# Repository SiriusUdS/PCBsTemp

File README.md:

# STM32 Rocket Engine Control Template

Template repository for STM32 embedded development projects focused on rocket engine control systems. This project uses CMake and is structured with a layered architecture for maintainability and modularity.

Repository name format: `<stm[model]|py|desktop>-<project_name>-<layer>`

## Project Structure

The project follows a layered architecture with clear separation of concerns:

```
├── src/
│   ├── HAL/              # Hardware Abstraction Layer
│   ├── Components/       # Hardware component drivers
│   ├── DIL/              # Device Interface Layer
│   └── Controller/       # Application logic and control algorithms
├── include/
│   ├── HAL/
│   ├── Components/
│   ├── DIL/
│   └── Controller/
├── cmake/                # CMake toolchain files
├── CMakeLists.txt        # Main build configuration
├── startup_stm32f407xx.s # Startup assembly file
└── STM32F407VGTx_FLASH.ld # Linker script
```

### Architecture Layers

#### 1. HAL (Hardware Abstraction Layer)
- Lowest level interface to hardware peripherals
- Direct access to STM32 registers and peripherals
- Provides basic initialization and control functions for GPIO, timers, ADC, UART, etc.

**Files:**
- `include/HAL/hal_init.h`
- `src/HAL/hal_init.c`
- `include/HAL/stm32f4xx.h`

#### 2. Components Layer
- Hardware component drivers for sensors, actuators, and communication modules
- Abstracts specific hardware components (sensors, valves, etc.)
- Uses HAL layer for low-level operations

**Files:**
- `include/Components/sensors.h`
- `src/Components/sensors.c`

#### 3. DIL (Device Interface Layer)
- High-level, abstract interface to devices
- Hides component-specific implementation details
- Provides logical device operations (e.g., engine control, valve management)

**Files:**
- `include/DIL/engine_interface.h`
- `src/DIL/engine_interface.c`

#### 4. Controller Layer
- Highest level application logic
- Implements control algorithms and state machines
- Orchestrates all lower layers for complete application functionality

**Files:**
- `include/Controller/controller.h`
- `src/Controller/controller.c`

## Prerequisites

### Required Software

1. **ARM GCC Toolchain**
   - Download from: https://developer.arm.com/tools-and-software/open-source-software/developer-tools/gnu-toolchain/gnu-rm
   - Add to system PATH

2. **CMake** (version 3.20 or higher)
   - Download from: https://cmake.org/download/
   - Or install via package manager:
     ```bash
     # Ubuntu/Debian
     sudo apt-get install cmake
     
     # macOS
     brew install cmake
     ```

3. **Build Tools**
   - Linux: `sudo apt-get install build-essential`
   - macOS: Install Xcode Command Line Tools
   - Windows: Install MinGW or use WSL

4. **ST-Link Utility** (for flashing)
   - Download from STMicroelectronics website
   - Or use OpenOCD: `sudo apt-get install openocd`

### Optional Tools

- **STM32CubeMX**: For peripheral configuration and HAL code generation
- **Serial Terminal**: PuTTY, minicom, or screen for UART communication
- **IDE**: Visual Studio Code, CLion, or STM32CubeIDE

## Setup Instructions

### 1. Clone the Repository

```bash
git clone <repository-url>
cd template
```

### 2. Configure for Your Target MCU

Edit `CMakeLists.txt` to match your specific STM32 target:

```cmake
# Update these lines for your MCU
set(MCU_FAMILY STM32F4xx)
set(MCU_MODEL STM32F407xx)
set(MCU_LINKER_SCRIPT "${CMAKE_SOURCE_DIR}/STM32F407VGTx_FLASH.ld")
```

If using a different STM32 model:
1. Update the linker script (`.ld` file) with correct memory sizes
2. Update the startup file (`.s` file) with correct vector table
3. Update CPU flags in CMakeLists.txt if needed

### 3. Build the Project

#### Using Command Line

```bash
# Create build directory
mkdir build
cd build

# Configure CMake with ARM toolchain
cmake .. -DCMAKE_TOOLCHAIN_FILE=../cmake/arm-none-eabi-gcc.cmake

# Build the project
cmake --build .
```

This will generate:
- `STM32_RocketEngine.elf` - ELF executable
- `STM32_RocketEngine.hex` - Intel HEX format for flashing
- `STM32_RocketEngine.bin` - Binary format for flashing
- `STM32_RocketEngine.map` - Memory map file

#### Using Make

```bash
cd build
make
```

### 4. Flash to MCU

#### Using ST-Link

```bash
# Using st-flash
st-flash write STM32_RocketEngine.bin 0x8000000

# Or using OpenOCD
openocd -f interface/stlink.cfg -f target/stm32f4x.cfg -c "program STM32_RocketEngine.elf verify reset exit"
```

#### Using STM32CubeProgrammer

1. Open STM32CubeProgrammer
2. Connect to the board via ST-Link
3. Load the `.hex` or `.bin` file
4. Click "Download"

### 5. Debug

#### Using GDB

```bash
# Start OpenOCD (in one terminal)
openocd -f interface/stlink.cfg -f target/stm32f4x.cfg

# Start GDB (in another terminal)
arm-none-eabi-gdb build/STM32_RocketEngine.elf
(gdb) target remote localhost:3333
(gdb) monitor reset halt
(gdb) load
(gdb) continue
```

## Development Workflow

### Adding New Features

1. **New Sensor/Component**
   - Add header in `include/Components/`
   - Implement in `src/Components/`
   - Update CMakeLists.txt if needed

2. **New Device Interface**
   - Add header in `include/DIL/`
   - Implement in `src/DIL/`
   - Use Components layer functions

3. **New Control Logic**
   - Add to `include/Controller/controller.h`
   - Implement in `src/Controller/controller.c`
   - Use DIL functions

### Customization

#### Changing MCU Target

1. Update `CMakeLists.txt`:
   - Change `MCU_FAMILY` and `MCU_MODEL`
   - Update CPU flags (`CPU`, `FPU`, `FLOAT_ABI`)
   
2. Replace linker script (`.ld`) with your MCU's memory layout

3. Replace startup file (`.s`) with your MCU's vector table

4. Update `stm32f4xx.h` or include proper CMSIS headers

#### Adding STM32 HAL Library

If you want to use the official STM32 HAL library:

1. Download STM32CubeF4 package
2. Copy HAL sources to your project
3. Update CMakeLists.txt to include HAL sources
4. Replace minimal `stm32f4xx.h` with official CMSIS headers

## Project Configuration

### Compiler Flags

Defined in `CMakeLists.txt`:
- `-Wall -Wextra`: Enable warnings
- `-fdata-sections -ffunction-sections`: Enable garbage collection of unused sections
- `-O0 -g3`: Debug build (no optimization, full debug info)
- `-O2`: Release build (optimize for speed)

### Linker Flags

- `-specs=nano.specs`: Use newlib-nano for smaller code size
- `--gc-sections`: Remove unused sections
- `-Wl,-Map=`: Generate map file

## Troubleshooting

### Build Errors

**"arm-none-eabi-gcc not found"**
- Install ARM GCC toolchain and add to PATH
- Verify with: `arm-none-eabi-gcc --version`

**"undefined reference to"**
- Check that all source files are included in CMakeLists.txt
- Verify function declarations match implementations

### Flash Errors

**"Could not find device"**
- Check ST-Link connection
- Install ST-Link drivers
- Try different USB port

**"Flash loader run error"**
- Verify correct linker script for your MCU
- Check memory addresses in linker script
- Ensure binary size doesn't exceed flash memory

### Runtime Issues

**Program doesn't start**
- Check vector table location
- Verify startup code matches MCU
- Check clock configuration

**Hard fault**
- Enable fault handlers in startup code
- Use debugger to find fault location
- Check stack size in linker script

## Additional Resources

- [STM32F4 Reference Manual](https://www.st.com/resource/en/reference_manual/dm00031020.pdf)
- [ARM Cortex-M4 Technical Reference Manual](https://developer.arm.com/documentation/100166/0001/)
- [CMake Documentation](https://cmake.org/documentation/)
- [GNU ARM Embedded Toolchain](https://developer.arm.com/tools-and-software/open-source-software/developer-tools/gnu-toolchain/gnu-rm)

## Safety Notice

This template is designed for rocket engine control systems. Always follow proper safety protocols:
- Implement multiple safety interlocks
- Test thoroughly in simulation before hardware testing
- Have emergency shutdown procedures
- Follow all applicable regulations and safety standards
- Never operate engine systems without proper safety equipment and trained personnel

## License

This is a template project. Add your license information here.

## Contributing

Contributions are welcome. Please follow the existing code structure and layered architecture when submitting changes.

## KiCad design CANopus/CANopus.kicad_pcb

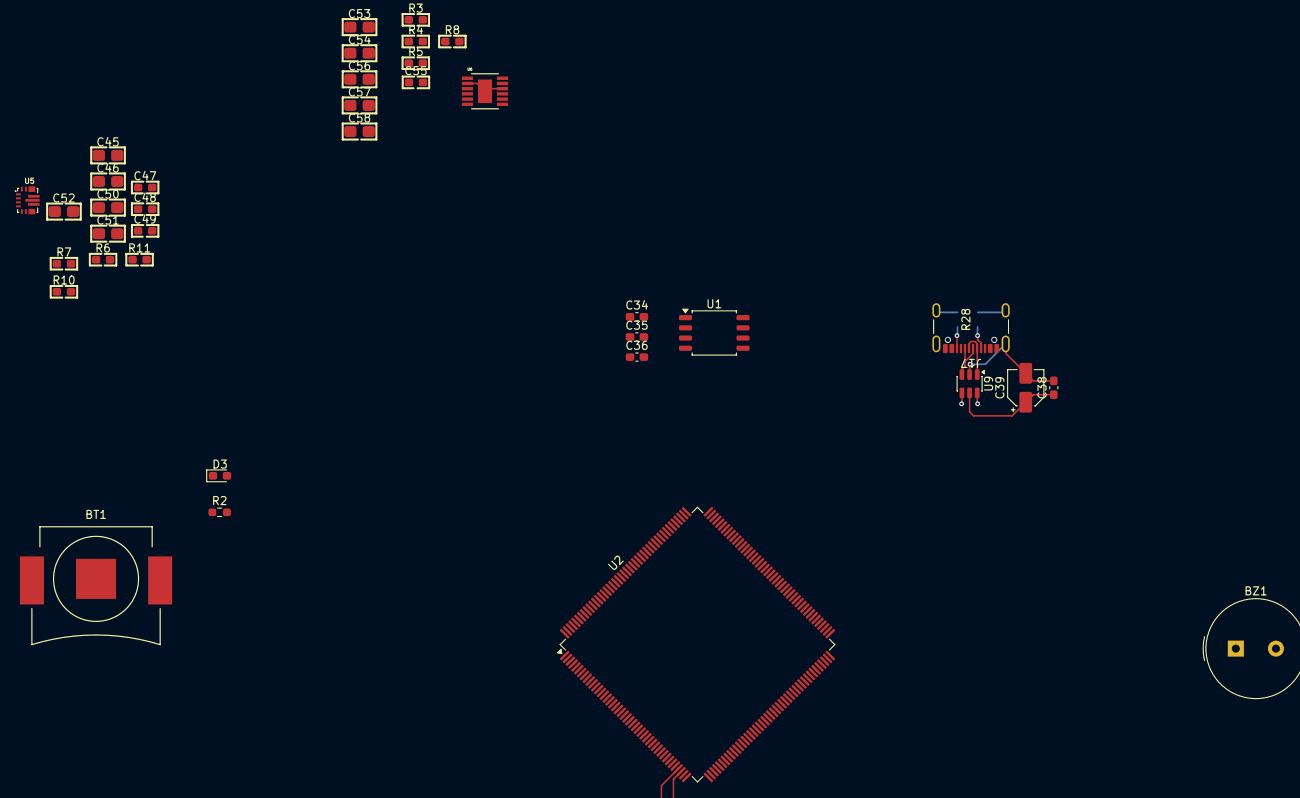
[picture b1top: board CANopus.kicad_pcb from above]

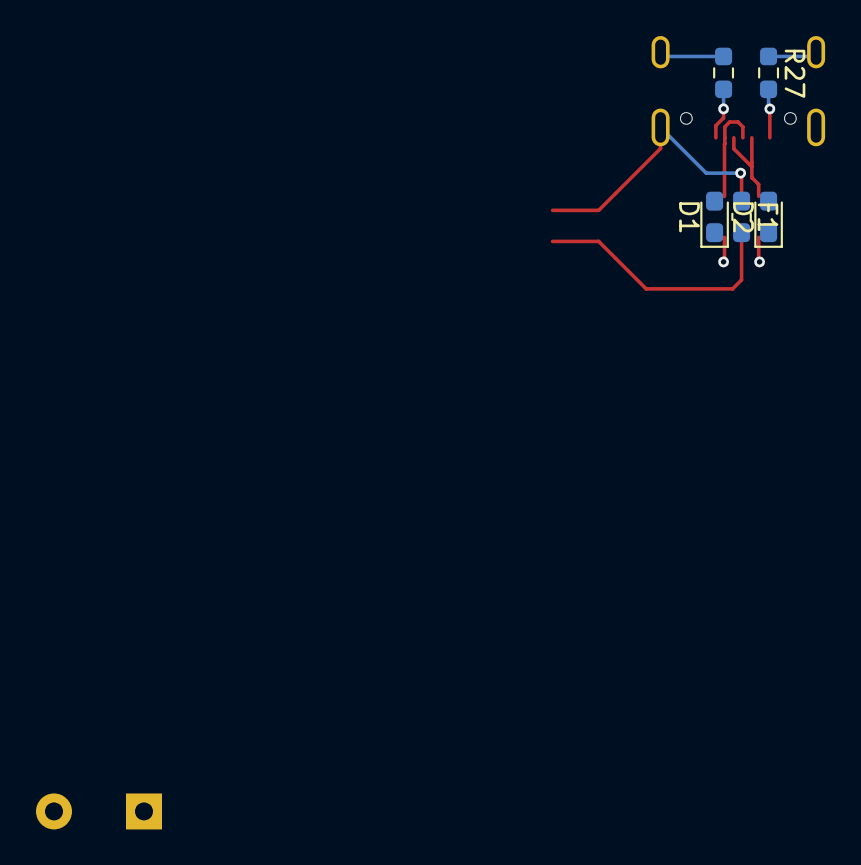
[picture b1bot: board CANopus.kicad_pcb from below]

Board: 2 copper layers, 42 parts (5 on the bottom side), 26 nets.

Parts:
BT1: Battery_Holder_1025; BatteryHolder_BHX1_1025
BZ1: Buzzer_TDK_PS1240; Buzzer_TDK_PS1240P02BT_D12.2mmP5mm
C34: 0.1u; C_0603_1608Metric_Pad1.08x0.95mm_HandSolder
C35, C38: 0.1uF; C_0603_1608Metric_Pad1.08x0.95mm_HandSolder
C36: 0.47uF; C_0603_1608Metric_Pad1.08x0.95mm_HandSolder
C39: 10uF/50V; CP_Elec_4x5.4
C45, C46: 10u; C0805_MAN
C47, C49: 10u; C0603_MAN
C48, C55: 100n; C0603_MAN
C50, C51, C52: 22u; C0805_MAN
C53, C54: 4.7u; C0805_MAN
C56: 390pF; C0805_MAN
C57: 10pF; C0805_MAN
C58: 22uF; C0805_MAN
D1: D; D_0603_1608Metric_Pad1.05x0.95mm_HandSolder
D2, D3: 6.4V; D_0603_1608Metric_Pad1.05x0.95mm_HandSolder
F1: Polyfuse; Fuse_0603_1608Metric_Pad1.05x0.95mm_HandSolder
J17: USB_C_Receptacle_USB2.0_man; USB_C_Receptacle_GCT_USB4105-xx-A_16P_TopMnt_Horizontal
R2: 10k; R_0603_1608Metric_Pad0.98x0.95mm_HandSolder
R3: 57.6k; R0603_MAN
R4, R5: x; R0603_MAN
R6: 470k; R0603_MAN
R7: 10k; R0603_MAN
R8: 210k; R0603_MAN
R10: 100k; R0603_MAN
R11: 150k; R0603_MAN
R27, R28: 5.1k; R_0603_1608Metric_Pad0.98x0.95mm_HandSolder
U1: SST25VF080B-50-4x-S2Ax; SOIC-8_5.3x5.3mm_P1.27mm
U2: STM32H747IITx; LQFP-176_24x24mm_P0.5mm
U5: TPS63070RNMT; QFN50P250X300X100-15N
U6: MSOP-12_MSE
U9: USBLC6-2SC6; SOT-23-6

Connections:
+3.3V: C49.1, C50.1, C51.1, C52.1, R6.1, R10.1
+3V3: C34.1, C35.1, C36.1, U1.8 (VDD)
+5V: C38.1, C39.1, D1.1 (K), U9.5 (VBUS)
+BATT: C45.1, C46.1, C47.1, R7.1
/ECU_Power/3.3V_FB: R6.2, R11.1
/USB_D+: J17.A6 (D+), J17.B6 (D+), U9.3 (I/O2)
/USB_D-: J17.A7 (D-), J17.B7 (D-), U9.1 (I/O1)
GND: BT1.2 (-), C34.2, C35.2, C36.2, C38.2, C39.2, C45.2, C46.2, C47.2, C48.1, C49.2, C50.2, C51.2, C52.2, C53.2, C54.2, C56.2, C57.2, C58.2, D2.2 (A), D3.2 (A), J17.A1 (GND), J17.A12 (GND), J17.B1 (GND), J17.B12 (GND), R2.1, R3.2, R5.2, R11.2, R27.1, R28.1, U1.4 (VSS), U2.6 (VSS), U2.12 (VSS), U2.24 (VSS), U2.45 (VSS), U2.47 (VSS), U2.64 (VSS), U2.70 (VSS), U2.81 (VSS), U2.83 (VSS), U2.93 (VSS), U2.100 (VSS), U2.112 (VSS), U2.119 (VSS), U2.134 (VSS), U2.137 (VSS), U2.151 (VSS), U2.159 (VSS), U2.173 (VSS), U6.2 (PGND), U6.10 (SGND), U6.13 (PGND), U9.2 (GND)
unnamed: C56.1, C57.1, R8.1
unnamed: D1.2 (A), D2.1 (K), F1.2
unnamed: C53.1, U6.3 (Vin)
unnamed: F1.1, J17.A4 (VBUS), J17.A9 (VBUS), J17.B4 (VBUS), J17.B9 (VBUS)
unnamed: J17.A5 (CC1), R28.2
unnamed: J17.B5 (CC2), R27.2
unnamed: C55.2, U6.12 (CAP)
unnamed: R4.2, R5.1, U6.8 (FB)
unnamed: R3.1, U6.6 (RT)
unnamed: R8.2, U6.7 (VC)
unnamed: C54.1, U6.5 (VCC)
unnamed: C55.1, C58.1, R4.1, U6.11 (Vout)
VBAT: BT1.1 (+), U2.8 (VBAT)
VCAP: U2.80 (VCAP), U2.133 (VCAP), U2.172 (VCAP)
VDDDSI: U2.102 (VDD12DSI), U2.108 (VDD12DSI)
VDDLDO: U2.82 (VDDLDO), U2.135 (VDDLDO), U2.175 (VDDLDO)
VDD_MCU: U2.7 (VDD), U2.13 (VDD), U2.25 (VDD), U2.44 (VDD), U2.48 (VDD), U2.65 (VDD), U2.71 (VDD), U2.84 (VDD), U2.92 (VDD), U2.99 (VDD), U2.113 (VDD), U2.126 (VDD), U2.136 (VDD), U2.152 (VDD), U2.160 (VDD), U2.176 (VDD)
VSSDSI: U2.105 (VSSDSI), U2.109 (VSSDSI)

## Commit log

2025-11-02 Initialize copilot/create-cmake-template-project
2025-11-15 Pages cleanup
2025-11-15 library
2025-11-16 Analog modifs
2025-11-16 Alim
